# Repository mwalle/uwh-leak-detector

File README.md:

# Underwater Housing Leak Detector

Monitors the underpressure of your underwater housing and notifies you of
any leaks.

## Features

The leak detector provides the following features:

- Optical and acoustical alarm. Red and green LED to indicate the current
  health. Piezo buzzer to get the user's attention.
- Powered by just one CR2032 coin cell.
- Very long battery life, works down to 1.8V cell voltage.
- Battery monitoring. Indicates low-battery during idle mode.
- Hackable design using a Microchip ATtiny microcontroller
- MEMS pressure sensor. Supports two different devices: Bosch BMP581 and
  STMicro LPS22HB.
- Demo mode. Test any changes by a simulated sensor.
- Optical UART debug mode. The red LED can be used as a serial port. The
  receiver consists of a photo transistor and a bipolar transistor in a
  darlington configuration and an UART-to-USB adapter.
- Different modes selectable by the reset button.
- Extremely small.
- Open Hardware and Open Firmware schematics and layout as well as firmware
  sources are free for everyone.

## User's manual

TBD

## Mode of operation

Most functionality revolves around the microcontroller polling the pressure
sensor at a low frequency and then go (back) to sleep. The goal is to be in
sleep mode most of the time to save precious battery power. The
microcontroller runs with a system clock of 1MHz. The assumption is that a
slower clock frequency will preserve more power. But it is not clear whether
this is true; it might as well save more power if the microcontroller can
go back to sleep faster. One would need to do power consumption
measurements to evaluate which is better.

There are basically two different modes:
- Idle mode. The detector waits for a pressure drop to go into supervisor
  mode. In this mode, the pressure is polled every two seconds.
- Supervisor mode. The detector monitors the pressure at a faster rate and
  drives the dual-color LED/buzzer to show the state to the user.

Internally, the firmware consists of a [state
machine](firmware/main.c#L49). The state maps to the external indications
at any time. E.g. if the program is in state `ALARM`, the LED is flashing
red and the buzzer is enabled.

The firmware is able to count the number of reset button presses. Depending
on this the firmware enters different modes:
- Normal mode
- Debug mode. Red LED is used to transmit debug information.
- Demo mode. Instead of reading the real pressure, predefined measurements
  are replayed.
- Demo mode with debug. Combines demo and debug mode.
- Power-off mode. Turn off periodic watchdog interrupt. Only an external
  reset can wake up the microcontroller.

### ATtiny hardware block usage

The *Timer/Counter0* is used to stimulate the piezo buzzer with a 2kHz
frequency.

The *Timer/Counter1* is either used in PWM mode to dim the LEDs or to drive
the software UART. Both are mutually exclusive and the startup will choose
between these two.

The *Universal Serial Interface* is used for the I2C communication with the
pressure sensor. There is no receiving ACK handling (yet).

The *Watchdog timer* is used in interrupt mode as a wake up source. It will
wake up the microcontroller either every 250ms or every 2s, depending on
the mode. Additionally, it is used for timekeeping by counting ticks.

The *Analog to Digital Converter* is used in reverse mode (AREF is VCC and
the measurement is the internal band gap voltage) to measure the battery
voltage.

The *Analog Comparator` is unused and disabled on start-up.

The hardware is prepared to use interrupts via the *Pin Change Interrupt`
but it is unused. The sensor supports to constantly measure the pressure
and generate an interrupt if it is outside a predefined window. But it is
very limited in this regard, thus it not used for the time being.

### Supported pressure sensors

The firmware supports two different pressure sensors:
- [Bosch Sensortec
  BMP581](https://www.bosch-sensortec.com/products/environmental-sensors/pressure-sensors/bmp581/)
- [STMicroelectronics
  LPS22HB](https://www.st.com/en/mems-and-sensors/lps22hb.html)

They share the same footprint and can be used with the same PCB. The BMP581
is more advanced regarding its features, but most of them are unused. One
major drawback is the package and metal can of the sensor. There is a tiny
hole in the can which sometimes clogs and the sensor will measure bogus
values. Also, it isn't easy to convert the raw value of the sensor to
millibars. It will need division routines which takes up a lot of code
space.

The LPS22HB is a rather old sensor and consumes more power. It's package
doesn't have any holes but an exposed silicon area to sense the pressure.
Therefore, it is not prone to clogging like the BMP581. Also the register
interface seems to be more thought through. There are also successors of
the LPS22HB which need less power. Unfortunately, they aren't available at
the moment.

### Resource usage

TBD

## Programming the microcontroller

The board features a [Tag-Connect](https://www.tag-connect.com) with the
standard 6pin header AVR pinout. The microcontroller can be programmed
using the simple SPI based programming protocol. There is no need for
high-voltage programming.

## Schematics

The schematics are available [here](hardware/leak-detector.pdf).

## Bill Of Materials

| Ref | Qty | Part | Footprint |
| --- | --- | --- | --- |
| R1 | 1 | 33Ω Resistor | 0603 |
| R2, R7 | 2 | 1kΩ Resistor | 0603 |
| R3 | 1 | 10Ω Resistor | 0603 |
| R4, R5 | 2 | 100Ω Resistor | 0603 |
| R6, R8, R9 | 3 | 10kΩ Resistor | 0603 |
| D1 | 1 | Dual-color LED | - |
| U1 | 1 | BMP581/LPS22HB pressure sensor | LGA-10 |
| U2 | 1 | ATtiny25V | SOIC-8 |
| SW2 | 1 | PTS810 Push Button | - |
| BT1 | 1 | CR2032 Coin Cell Holder | - |
| BZ1 | 1 | Visaton 3580 Piezo Buzzer | - |

## Kits and PCBs

If you need a PCB, a kit or an assembled and pre-programmed board, contact
me at <uwh-leak-detector@walle.cc>.

## License

The schematics and layout is licensed under the CERN-OHL-S v2. The firmware
source is licensed under the GNU General Public License v3.0.

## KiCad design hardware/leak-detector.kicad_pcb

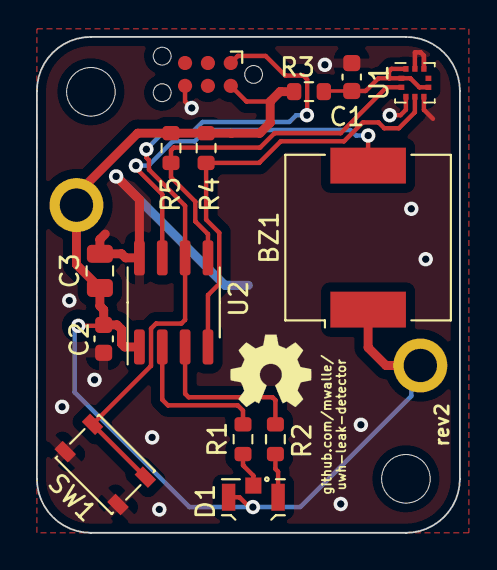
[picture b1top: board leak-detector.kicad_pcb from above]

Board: 2 copper layers, 23.5 x 27.5 mm, 17 parts (1 on the bottom side), 11 nets.

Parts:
BT1: CR2032; BatteryHolder_Keystone_2899_1x2032
BZ1: Visaton 3580; Buzzer_CUI_CPT-9019S-SMT
C1, C2: 100n; C_0603_1608Metric
C3: 10u; C_0805_2012Metric
D1: Everlight 12-22; LED_LiteOn_LTST-S326
H1, H2: MountingHole; MountingHole_2.7mm_M2.5
J1: Conn_Atmel_ISP_TagConnect_TC2030; Tag-Connect_TC2030-IDC-NL_2x03_P1.27mm_Vertical
R1: 100R; R_0603_1608Metric
R2: 560R; R_0603_1608Metric
R3: 10R; R_0603_1608Metric
R4, R5: 10k; R_0603_1608Metric
SW1: PTS810; SW_SPST_PTS810
U1: LPS22HH; Bosch_LGA-10_2x2mm_P0.5mm
U2: ATtiny412; SOIC-8_3.9x4.9mm_P1.27mm

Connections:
/BUZZER: BZ1.2 (+), U2.7 (PA3)
/LED_GREEN: R2.2, U2.3 (PA7)
/LED_RED: R1.2, U2.2 (PA6)
/SCL: R5.2, U1.2 (SCL), U2.5 (PA2)
/SDA: R4.2, U1.4 (SDA), U2.4 (PA1)
/~RST/UPDI: J1.1 (UPDI), SW1.2, U2.6 (~RESET/PA0)
GND: BT1.2 (-), C1.2, C2.2, C3.2, J1.6 (GND), SW1.1, U1.3 (RES), U1.5 (SDO), U1.8 (GND), U1.9 (GND), U2.8 (GND)
unnamed: C1.1, R3.1, U1.1 (VDDIO), U1.6 (CS), U1.10 (VDD)
unnamed: D1.1 (K1), R2.1
unnamed: D1.2 (K2), R1.1
VCC: BT1.1 (+), BZ1.1 (-), C2.1, C3.1, D1.3 (A), J1.2 (VCC), R3.2, R4.1, R5.1, U2.1 (VCC)

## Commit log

2023-03-05 hardware: initial commit
2023-03-05 firmware: initial commit
2023-03-14 firmware: add ADC support
    Add battery voltage tracking. Use the external Vcc (the battery voltage)
    as reference and measure the internal bandgap voltage. Then use the
    inverse function of the ADC formulae to infer the battery voltage.
2023-03-16 firmware: swuart: use 9600 baud
    It turns out, the hardware is able to go faster. 9600 baud seems to on
    the edge what is possible to do with the 1MHz system clock and software
    UART.
2023-03-16 firmware: sensor OOR mode and major rework
    Add support for the out-of-range mode of the pressure sensor. The idea
    is that the sensor could wake the µC and the µC doesn't have to poll the
    sensor periodically. Unfortunately, the sensor is only able the maximum
    range is just about +/-2.55mbar.
    Also document our states, move the state handling into a function.
2023-03-16 firmware: adc: only enable ADC during measurement
    The battery voltage is just measured once in a while. Enable the ADC
    block only when needed.
2023-03-16 firmware: bmp581: remove OOR mode
    It turns out, the mode doesn't work reliably. Let the µC just poll the
    sensor in power down mode.
2023-03-16 firmware: buzzer: use timer0 and add buzzer_init()
    Now that timer1 is used by the software UART, use timer0 for the buzzer.
    Also, move the timer setup into buzzer_init() and only enable and
    disable the timer and output in buzzer_{on,off}().
2023-03-16 firmware: led: rework LED handling
    Introduce led_init() and don't use update_led() in the selftest. Instead
    let the selftest set the appropriate bits itself.
2023-03-16 firmware: mainloop: poll the pressure in powered-down mode
    If the pressure is within the "normal" range. Reconfigure the watchdog
    to just wake the µC up every 2s to poll the pressure. Introduce a new
    threshold p_on_off to move into idle mode if it's exceeded.
2023-03-16 firmware: disable unused blocks
    For now, it is only the analog comparator module.
2023-03-16 firmware: rework print_status()
2023-03-16 firmware: mainloop: trigger sensor read before power-down
    Instead of waiting for the sensor to complete the measurement within the
    active cycle, just start a measurement at the end and read the results
    at the start of the next cycle.
2023-03-16 firmware: swuart: change to timer1
    Use timer1 for the swuart. The timer1 needs more power than timer0 and
    in normal mode, the UART isn't used. Thus, use timer1 for the UART.
    Timer0 can later be used to drive the LEDs in PWM mode.
2023-03-16 firmware: mainloop: go back to sleep if ticks haven't advanced
    Any interrupt might wake the µC. If the ticks didn't change, that is
    there was no watchdog interrupt. Just go back to sleep.
2023-03-16 firmware: enable -Wl,--sections
    Put each function into an own section and let the linker discard unused
    functions. Will preserve precious program space.
2023-03-16 firmware: add demo sensor support
    Add a new demo mode. If activated, that sensor will return mocked values
    for the pressure reading.
    To activate that mode, the user has to reset the board four or five
    times in a row.
2023-03-17 firmware: introduce sensor class
    Factor out all the sensor handling. Move the demo sensor into an own
    module. This way, additional sensor support only need to implement some
    sensor ops in its own module.
2023-03-17 firmware: move buzzer into own module
    Move the buzzer handling into an own module and get rid of the
    update_buzzer(). The buzzer module can use an ISR to toggle the buzzer
    itself.
2023-03-17 firmware: setup: clear watchdog flag before enabling interrupts
    The watchdog flag might already be set before we use it and thus the
    watchdog timer ISR is immediately triggered after enabling interrupts.
    That will already increase the ticks by one. Avoid that by clearing that
    flag.
2023-03-17 firmware: move all macros to the top of the file
2023-03-17 firmware: add low battery indication
    The battery is measure during each cycle. If the voltage is below 2.9V
    set a flag which will change the LED pattern during idle mode to give
    the user an indication.
2023-03-17 firmware: add new silent alarm feature
    If a leak is detected the buzzer will be turned on. It is assumed that
    after some time, the user noticed the alarm and we can silence the
    beeper.
2023-03-17 firmware: slightly rework print_status()
2023-03-17 firmware: sensor: always return mbar
    Return sensor readings in mbar. This is the first step to support more
    than just one pressure sensor. All sensors will need to return the
    measurement in mbar. This will also simplify the code because the MBAR()
    and similar macros are not needed anymore. On the flipside, runtime
    division is now needed which increases the code size. But these routines
    are also needed for the status line printing.
2023-03-18 firmware: introduce compile options
    Make it configurable to exclude individual components from compilation.
    Start with the software UART. The compiler will take care of optimizing
    away any unused code and the linker won't complain about missing
    function calls.
2023-03-19 firmware: sensor: move one_shot() to sensor.h and convenience functions
    The one shot method can be implemented in the sensor class. There is no
    need that every sensor has its own implementation of it. While at it,
    provide handy sensor_*() functions.
2023-03-19 firmware: bmp581: just read two bytes pressure data
    No need to read all three bytes, if only two are used.
2023-03-19 firmware: support STM LPS22HB
    Add support for the STMicro LPS22HB pressure sensor.
2023-03-20 firmware: buzzer: enable pull-up resistor
    The pin might also be used as an open drain active-low interrupt line.
    Enable the pull-up because there is no external one.
2023-03-20 firmware: led: use PWM and make code smaller
    Use PWM for the LEDs to consume some power and make it the code smaller
    by encoding the LED control into the state variable.
2023-03-20 firmware: only call uart_init() when debug is enabled
2023-03-21 firmware: bmp581: remove temperature reading
    Remove the dead code.
2023-03-21 firmware: Makefile: enable -Werror
    From now on, no warning are allowed anymore.
2023-03-21 firmware: set the lower battery threshold to 2.7V
    CR2032 coin cells have around 10% capacity left when they reach 2.7V.
2023-03-21 firmware: don't track the led state
    Don't track the LED state, just update the LEDs every time.
2023-03-21 firmware: selftest: fix LED selftest
    With the recent PWM changes for the LEDs, a different handling for the
    selftest is needed.
2023-03-21 firmware: battery: do the battery check during selftest
    Measure the battery voltage at the end of the LED selftest. This way,
    the battery will be stressed before doing the measurement.
2023-03-22 firmware: make individual sensors configurable
2023-03-22 firmware: export ticks
2023-03-22 firmware: sort enum, macros and static variables
    Consolidate all macros, enum, structs and static variables.
2023-03-22 firmware: drop ctx->flags
    Use the global __flags instead.
2023-03-22 firmware: display voltage as floating point
2023-03-22 firmware: buzzer: drop the ISR handling
    The ISR will disturb the software UART, which also use ISRs. Instead
    call the update routine from the watchdog ISR.
2023-03-22 firmware: rename update_led() to __led_update()
2023-03-22 firmware: battery: measure voltage only every 8s
2023-03-22 firmware: kill all callbacks in the watchdog ISR
    Move the tick handling to the start of the mainloop. This way, most of
    the atomic sections can be dropped.
2023-03-22 firmware: drop unneeded includes
2023-03-22 firmware: move tick handling functions
2023-03-22 firmware: move watchdog handling
    Move the watchdog period handling out of the state machine handling into
    power_down().
2023-03-22 firmware: move buzzer function from module to the main module
2023-03-22 firmware: encode buzzer and led function into state
    Drop context::state and instead make it a global variable with a special
    encoding. This will save some code size.
2023-03-22 firmware: move the buzzer_tick() and led_tick()
    Move the buzzer_tick() and led_tick() after the state machine
    processing, which will update the buzzer and LED after the state change.
2023-03-22 firmware: make demo optional
2023-03-23 firmware: remove ticks.h
2023-04-04 firmware: introduce power-down mode
    Add a power-down mode to turn off everything which is possible. That is,
    turn off the watchdog and pin-change interrupts and go into sleep mode.
    The only wake up source is the reset button.
2023-04-04 add initial README.md
2023-04-12 README.md: fix grammar
    Thanks M. :)
2023-04-26 hardware: update to attiny412
2023-05-02 firmware: add banner
    Print a banner with version and detected sensor at startup.
2023-05-18 read tempearture (wip)
2023-05-18 firmware: begin conversion to attiny412
2023-05-19 read temperature fix
2023-05-19 zero ticks when entering IDLE
    Zero the ticks when entering IDLE mode.
2023-05-19 add recording feature
2023-05-19 add fuses
